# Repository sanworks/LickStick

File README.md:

# LickStick
A capacitive lick sensing device designed for Neuroscience research.

## Important Note ##
LickStick is in beta testing, and may still have unresolved issues.

## Contents ##
This repository includes:
* Circuit board and enclosure design files
* Link to Bill of Materials
* Firmware (Arduino language, requires Teensy board package)
* A MATLAB class to control the LickStick device

## Setup ##
* Add /LickStick/MATLAB/ to the MATLAB path
* Connect a LickStick device to your PC
* See comments in LickStick.m for usage

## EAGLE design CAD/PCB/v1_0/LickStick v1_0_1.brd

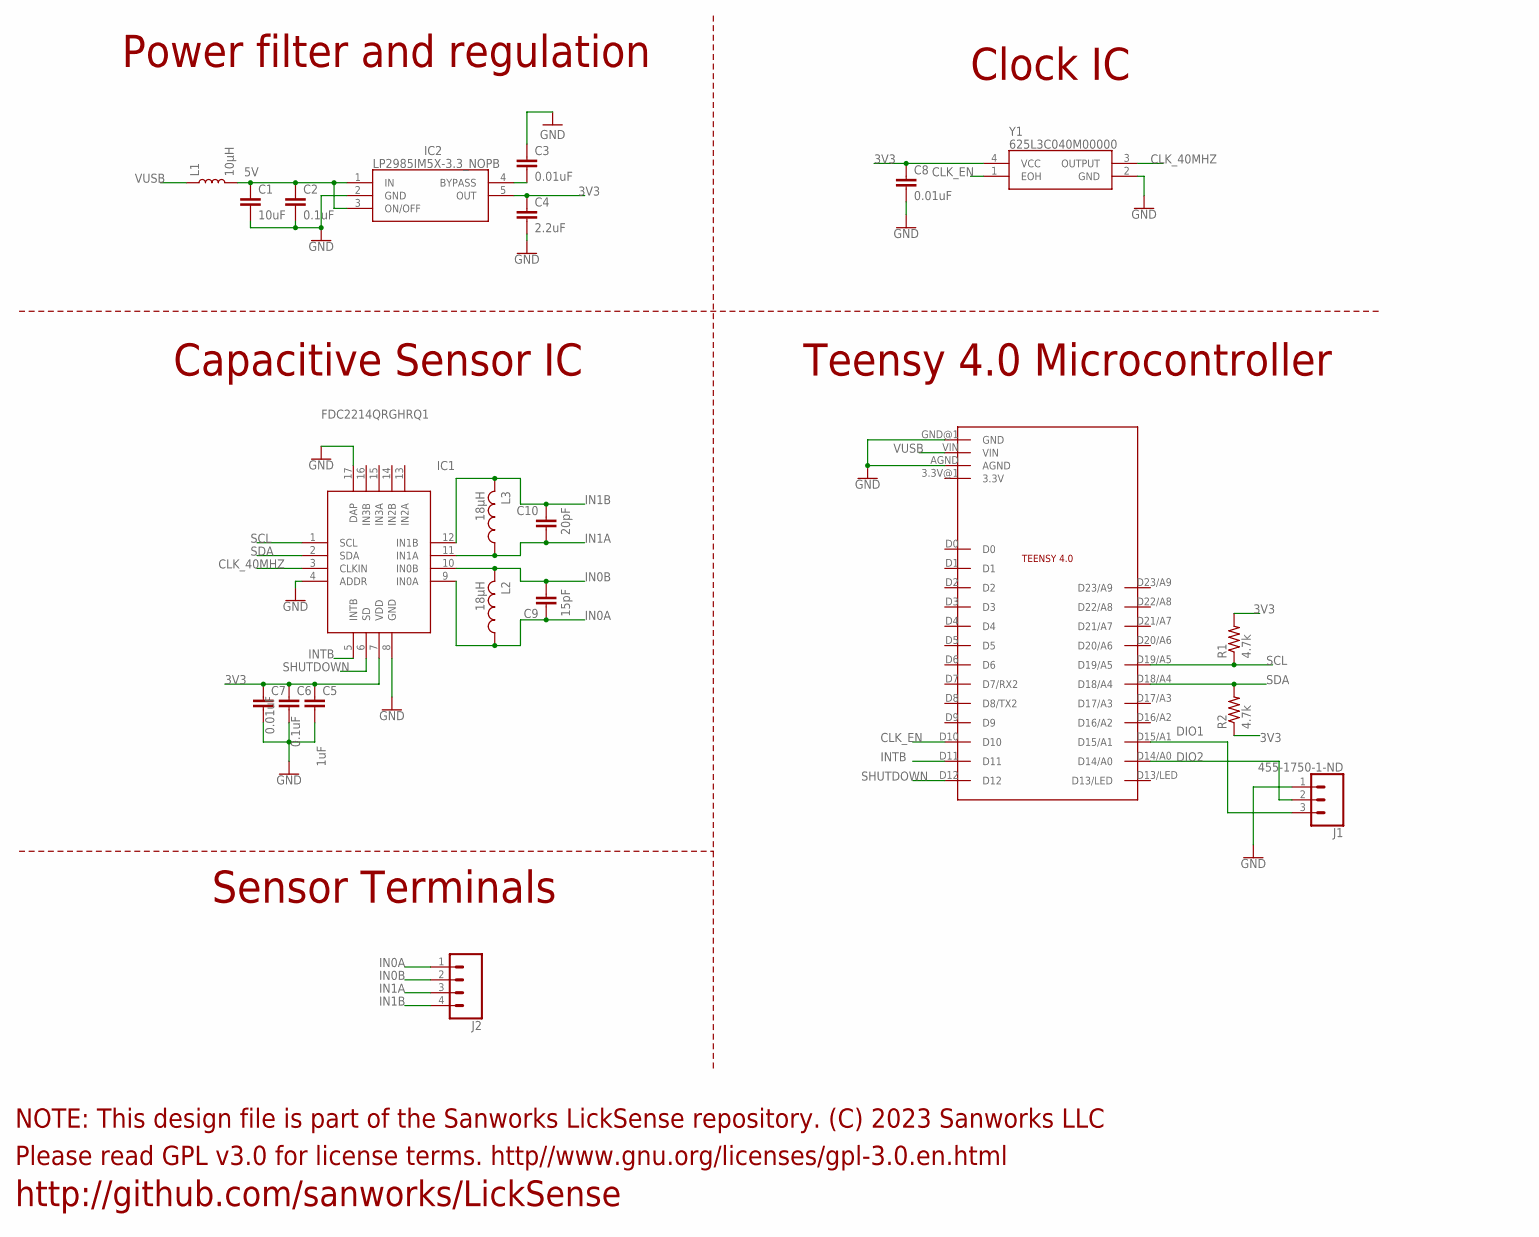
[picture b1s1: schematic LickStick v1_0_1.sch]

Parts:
C1: 10uF; 0805
C2, C6: 0.1uF; 0805
C3, C7, C8: 0.01uF; 0805
C4: 2.2uF; 0805
C5: 1uF; 0805
C9: 15pF; 0805
C10: 20pF; 0805
IC1: FDC2214QRGHRQ1; QFN50P400X400X80-17N
IC2: LP2985IM5X-3.3_NOPB; SOT95P280X145-5N
J1: 455-1750-1-ND; 1X03
J2: CONN_04PTH; 1X04
L1: 10μH; 0806
L2, L3: 18μH; L3225P
MC1: TEENSY4.0_SIMPLE_NO_VUSB
R1, R2: 4.7k; R0805
Y1: 625L3C040M00000

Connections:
3V3: C4.1, C5.1, C6.1, C7.1, C8.1, IC1.7 (VDD), IC2.5 (OUT), R1.2, R2.1, Y1.4 (VCC)
5V: C1.1, C2.1, IC2.1 (IN), IC2.3 (ON/OFF), L1.2
CLK_40MHZ: IC1.3 (CLKIN), Y1.3 (OUTPUT)
CLK_EN: MC1.D10, Y1.1 (EOH)
DIO1: J1.3, MC1.D15/A1
DIO2: J1.2, MC1.D14/A0
GND: C1.2, C2.2, C3.1, C4.2, C5.2, C6.2, C7.2, C8.2, IC1.4 (ADDR), IC1.8 (GND), IC1.17 (DAP), IC2.2 (GND), J1.1, MC1.AGND, MC1.GND@1 (GND), Y1.2 (GND)
IN0A: C9.1, IC1.9 (IN0A), J2.1, L2.1
IN0B: C9.2, IC1.10 (IN0B), J2.2, L2.2
IN1A: C10.1, IC1.11 (IN1A), J2.3, L3.1
IN1B: C10.2, IC1.12 (IN1B), J2.4, L3.2
INTB: IC1.5 (INTB), MC1.D11
unnamed: C3.2, IC2.4 (BYPASS)
SCL: IC1.1 (SCL), MC1.D19/A5, R1.1
SDA: IC1.2 (SDA), MC1.D18/A4, R2.2
SHUTDOWN: IC1.6 (SD), MC1.D12
VUSB: L1.1, MC1.VIN

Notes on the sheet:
Teensy 4.0 Microcontroller
Clock IC
Power filter and regulation
Capacitive Sensor IC
Sensor Terminals
Please read GPL v3.0 for license terms. http//www.gnu.org/licenses/gpl-3.0.en.html
NOTE: This design file is part of the Sanworks LickSense repository. (C) 2023 Sanworks LLC
http://github.com/sanworks/LickSense

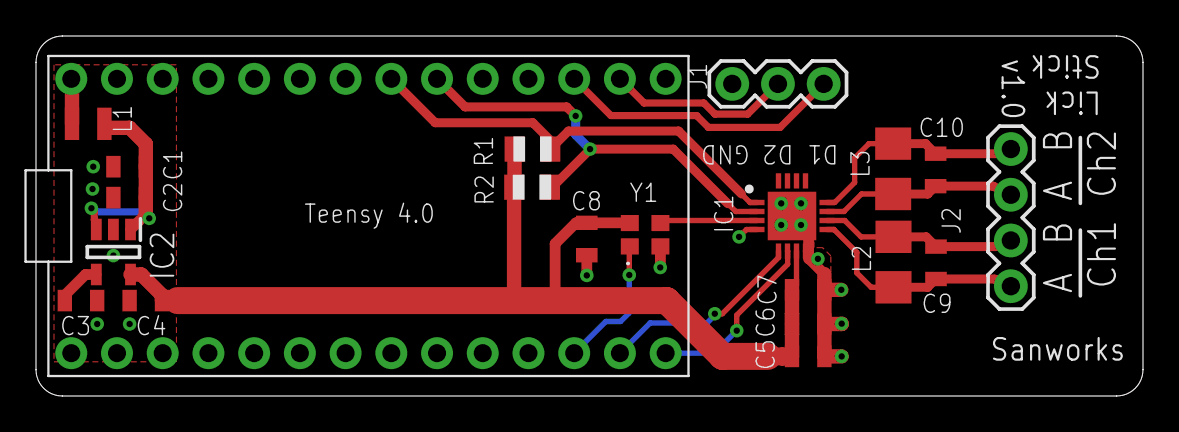
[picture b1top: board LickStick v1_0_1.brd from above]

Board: 2 copper layers, 61.5 x 20.0 mm, 21 parts (0 on the bottom side), 17 nets.

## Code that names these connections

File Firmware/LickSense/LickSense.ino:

/*
  ----------------------------------------------------------------------------

  This file is part of the Sanworks LickSense repository
  Copyright (C) Sanworks LLC, Rochester, New York, USA

  ----------------------------------------------------------------------------

  This program is free software: you can redistribute it and/or modify
  it under the terms of the GNU General Public License as published by
  the Free Software Foundation, version 3.

  This program is distributed  WITHOUT ANY WARRANTY and without even the
  implied warranty of MERCHANTABILITY or FITNESS FOR A PARTICULAR PURPOSE.
  See the GNU General Public License for more details.

  You should have received a copy of the GNU General Public License
  along with this program.  If not, see <http://www.gnu.org/licenses/>.

*/

#include <Wire.h>    // Arduino's builtin I2C class
#include "ArCOM.h"   // A wrapper to simplify transactions of different datatypes via USB serial
#include "FDC2214.h" // A class to interface with the Texas Instruments FDC2214 capacitive sensor IC

// Firmware version
#define FIRMWARE_VERSION 2

// Pin definitions
#define CLK_EN 10  // Clock enable
#define INTB 11    // Interrupt pin (configured below to report data ready)
#define SHTDWN 12  // Shutdown pin (used to reset device)
#define DIO1 15    // Digital I/O pin 1 (Middle position on green screw terminal header)
#define DIO2 14    // Digital I/O pin 2 (Right position on green screw terminal header)
#define LED_PIN 13 // LED

// Parameters
#define THRESH_DEFAULT 1900000 // Default touch detection threshold. Used from power-on until the PC connects.

// Setup interfaces
ArCOM USBCOM(Serial);
FDC2214 SensorIC(CLK_EN, INTB, SHTDWN);

// Timer used to read the sensor at even intervals
IntervalTimer readTimer;

// Program variables
byte opByte = 0;
byte inByte = 0;
byte usbStreaming = 0;
byte lickDetected = 0;
byte ledEnabled = 0;
uint16_t regValue = 0;
uint32_t thresholdValue = 0;
uint32_t nDebounceCycles = 20; // 20 cycles @ 2kHz sampling = 100Hz max licking
uint32_t debounceCounter = 0;
uint32_t nSamplesToReturn = 0;
union {
    uint8_t uint8[4];
    uint16_t uint16[2];
    uint32_t uint32[1];
} sensorValue;
union {
    byte byteArray[4];
    float floatVal;
} samplingInterval; // Hardware timer period in microseconds (500 = 2kHz). Set as a Union so it can be read as bytes.

void setup() {
  Wire.begin();
  SensorIC.init();
  pinMode(DIO1, OUTPUT);
  digitalWrite(DIO1, LOW);
  pinMode(DIO2, OUTPUT);
  digitalWrite(DIO2, LOW);
  pinMode(LED_PIN, OUTPUT);
  digitalWrite(LED_PIN, LOW);
  thresholdValue = THRESH_DEFAULT;
  samplingInterval.floatVal = 500;
  readTimer.begin(readCycle, samplingInterval.floatVal);
}

void loop() {
  if (USBCOM.available() > 0) {
    opByte = USBCOM.readByte();
    switch(opByte) {
      case 'F': // Return firmware version
        USBCOM.writeUint32(FIRMWARE_VERSION);
      break;
      case 'R': // Read sensor value
        nSamplesToReturn = USBCOM.readUint32();
        usbStreaming = 1;
      break;
      case 'S': // Start/stop USB streaming
        nSamplesToReturn = 0; // Continuous streaming
        usbStreaming = USBCOM.readByte();
      break;
      case 'W': // Set read count
        regValue = USBCOM.readUint16();
        SensorIC.set_RCOUNT(regValue);
      break;
      case 'N': // Set settle count
        regValue = USBCOM.readUint16();
        SensorIC.set_SETTLECOUNT(regValue);
      break;
      case 'D': // Set reference divider
        inByte = USBCOM.readUint8();
        SensorIC.set_REF_DIVIDER(inByte);
      break;
      case 'C': // Set drive current
        inByte = USBCOM.readUint8();
        SensorIC.set_DRIVE_CURRENT(inByte);
      break;
      case 'T': // Set threshold
        thresholdValue = USBCOM.readUint32();
      break;
      case '!': // Set active channel
        inByte = USBCOM.readByte();
        SensorIC.set_ACTIVE_CHANNEL(inByte);
      break;
      case 'I': // Set sampling interval
        USBCOM.readByteArray(samplingInterval.byteArray, 4);
        readTimer.end();
        readTimer.begin(readCycle, samplingInterval.floatVal);
      break;
      case 'L': // set LED enable/disable
        ledEnabled = USBCOM.readByte();
      break;
    }
  }
}

void readCycle() {
  sensorValue.uint32[0] = SensorIC.readSensor();
  if (debounceCounter == 0) {
    if (sensorValue.uint32[0] > thresholdValue) {
      setTTL(0);
      if (lickDetected == 1) {
        debounceCounter = nDebounceCycles;
      }
      lickDetected = 0;
    } else {
      setTTL(1);
      if (lickDetected == 0) {
        debounceCounter = nDebounceCycles;
      }
      lickDetected = 1;
    }
  } else {
    debounceCounter--;
  }
  bitWrite(sensorValue.uint8[0], 0, lickDetected); // Use LSB to encode lick detection. Bit is read and cleared on PC side
  if (usbStreaming) {
    USBCOM.writeUint32(sensorValue.uint32[0]);
    if (nSamplesToReturn > 0) {
      nSamplesToReturn--;
      if (nSamplesToReturn == 0) {
        usbStreaming = false;
      }
    }
  }
}

void setTTL(uint8_t level) {
  digitalWriteFast(DIO1, level);
  digitalWriteFast(DIO2, level);
  if (ledEnabled) {
    digitalWriteFast(LED_PIN, level);
  }
}

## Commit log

2023-12-07 -Added MATLAB firmware loading tool, LoadLickSenseFirmware.m with compiled binaries -Added tube mount CAD files -Improved comments in LickSense.m
2023-12-14 Add portString arg to clearTimers()
2023-12-15 -autoSetThreshold: Changed multiple of range
2023-12-23 -Stream GUI: Added option to set viewer time window -Updated default range multiple
2024-03-18 -Firmware: Updated to v2, added op to set sampling interval (previously fixed by macro) -MATLAB: Added support for configurable sampling rate -MATLAB stream UI: Fixed bug causing extra line in displa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
2024-05-14 Update README.md
    Updated name
2024-05-14 -Changed project name from LickSense to LickStick -Added design files for PCB v0.3
2024-06-25 -Added PCB v1.0.1 -Added enclosure v1.0 -MATLAB: Modded activeChannel numbers to match labels on device
2024-08-13 -Added STL for drink tube mount v0.2
2024-11-01 -MATLAB GUI: Added pushbuttons to increase/decrease threshold
2025-09-05 -Added initial draft of the Python interface. May be buggy.

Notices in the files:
parts and their libraries:
SparkFun-Coils: Licensing: Creative Commons ShareAlike 4.0 International - https://creativecommons.org/licenses/by-sa/4.0
